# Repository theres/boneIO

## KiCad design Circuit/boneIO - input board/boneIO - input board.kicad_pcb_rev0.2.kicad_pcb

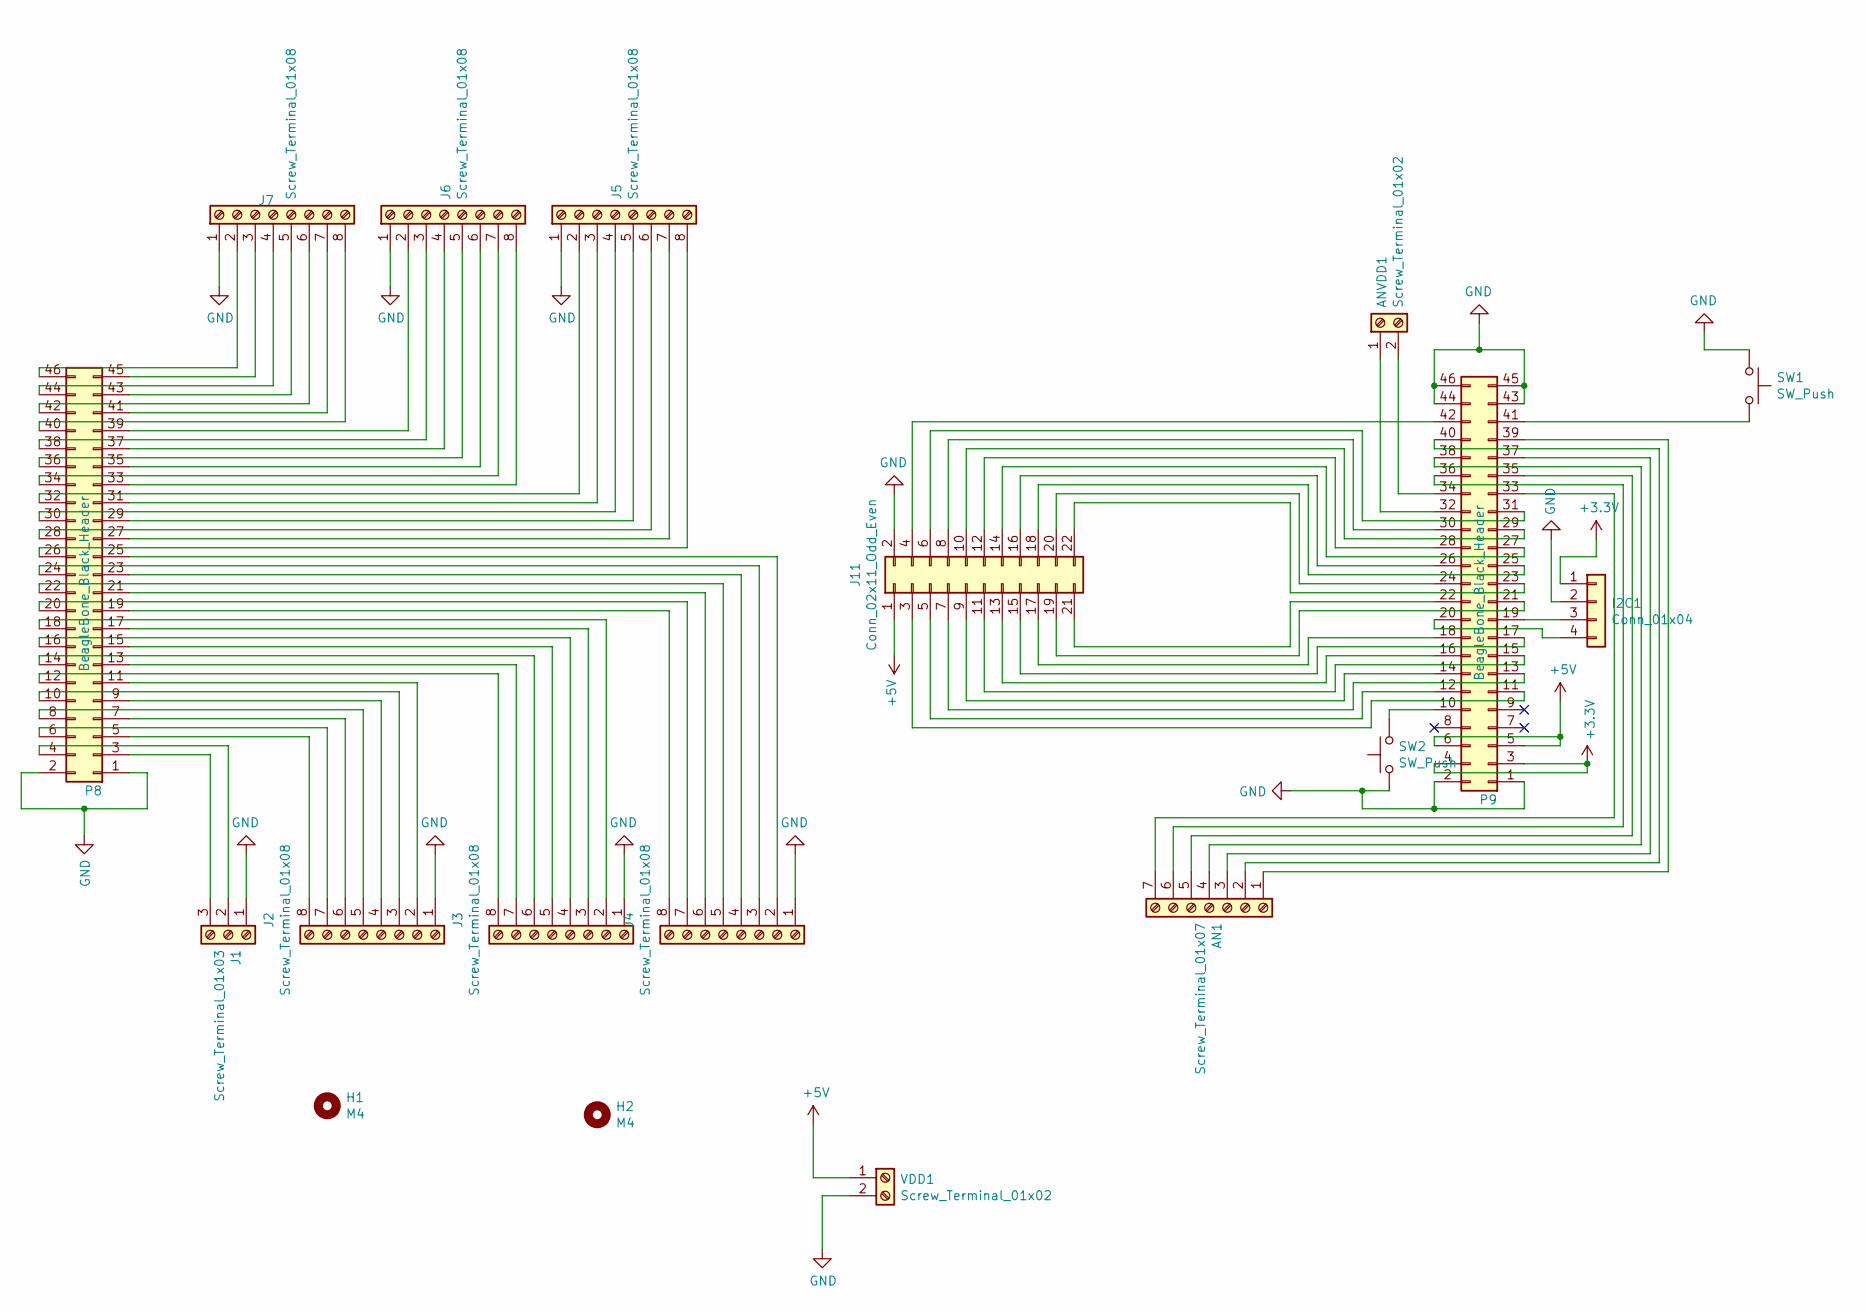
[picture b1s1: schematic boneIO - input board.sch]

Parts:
AN1: Screw_Terminal_01x07; TerminalBlock_RND_205-00017_1x07_P5.00mm_Horizontal
ANVDD1: Screw_Terminal_01x02; TerminalBlock_RND_205-00012_1x02_P5.00mm_Horizontal
H1, H2: M4; MountingHole_4.3mm_M4
I2C1: Conn_01x04; PinHeader_1x04_P2.54mm_Horizontal
J1: Screw_Terminal_01x03; TerminalBlock_RND_205-00013_1x03_P5.00mm_Horizontal
J2, J3, J4, J5, J6, J7: Screw_Terminal_01x08; TerminalBlock_RND_205-00018_1x08_P5.00mm_Horizontal
J11: Conn_02x11_Odd_Even; PinSocket_2x11_P2.54mm_Vertical
P8, P9: BeagleBone_Black_Header; PinHeader_2x23_P2.54mm_Vertical
SW1, SW2: SW_Push; SW_PUSH_6mm_H8mm
VDD1: Screw_Terminal_01x02; TerminalBlock_MetzConnect_Type171_RT13702HBWC_1x02_P7.50mm_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

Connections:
+3V3: I2C1.1, P9.3, P9.4
+5V: J11.1, P9.5, P9.6, VDD1.1
GND: I2C1.2, J1.1, J2.1, J3.1, J4.1, J5.1, J6.1, J7.1, J11.2, P8.1, P8.2, P9.1, P9.2, P9.43, P9.44, P9.45, P9.46, SW1.1, SW2.1, VDD1.2
unnamed: AN1.1, P9.39
unnamed: AN1.2, P9.40
unnamed: AN1.3, P9.37
unnamed: AN1.4, P9.38
unnamed: AN1.5, P9.35
unnamed: AN1.6, P9.36
unnamed: AN1.7, P9.33
unnamed: ANVDD1.1, P9.32
unnamed: ANVDD1.2, P9.34
unnamed: I2C1.3, P9.19
unnamed: I2C1.4, P9.20
unnamed: J1.2, P8.4
unnamed: J1.3, P8.3
unnamed: J2.2, P8.11
unnamed: J2.3, P8.10
unnamed: J2.4, P8.9
unnamed: J2.5, P8.8
unnamed: J2.6, P8.7
unnamed: J2.7, P8.6
unnamed: J2.8, P8.5
unnamed: J3.2, P8.18
unnamed: J3.3, P8.17
unnamed: J3.4, P8.16
unnamed: J3.5, P8.15
unnamed: J3.6, P8.14
unnamed: J3.7, P8.13
unnamed: J3.8, P8.12
unnamed: J4.2, P8.25
unnamed: J4.3, P8.24
unnamed: J4.4, P8.23
unnamed: J4.5, P8.22
unnamed: J4.6, P8.21
unnamed: J4.7, P8.20
unnamed: J4.8, P8.19
unnamed: J5.2, P8.32
unnamed: J5.3, P8.31
unnamed: J5.4, P8.30
unnamed: J5.5, P8.29
unnamed: J5.6, P8.28
unnamed: J5.7, P8.27
unnamed: J5.8, P8.26
unnamed: J6.2, P8.39
unnamed: J6.3, P8.38
unnamed: J6.4, P8.37
unnamed: J6.5, P8.36
unnamed: J6.6, P8.35
unnamed: J6.7, P8.34
unnamed: J6.8, P8.33
unnamed: J7.2, P8.46
unnamed: J7.3, P8.45
unnamed: J7.4, P8.44
unnamed: J7.5, P8.43
unnamed: J7.6, P8.42
unnamed: J7.7, P8.41
unnamed: J7.8, P8.40
unnamed: J11.3, P9.11
unnamed: J11.4, P9.42
unnamed: J11.5, P9.12
unnamed: J11.6, P9.31
unnamed: J11.7, P9.13
unnamed: J11.8, P9.30
unnamed: J11.9, P9.14
unnamed: J11.10, P9.29
unnamed: J11.11, P9.15
unnamed: J11.12, P9.28
unnamed: J11.13, P9.16
unnamed: J11.14, P9.27
unnamed: J11.15, P9.17
unnamed: J11.16, P9.26
unnamed: J11.17, P9.18
unnamed: J11.18, P9.25
unnamed: J11.19, P9.21
unnamed: J11.20, P9.24
unnamed: J11.21, P9.22
unnamed: J11.22, P9.23
unnamed: P9.10, SW2.2
unnamed: P9.41, SW1.2

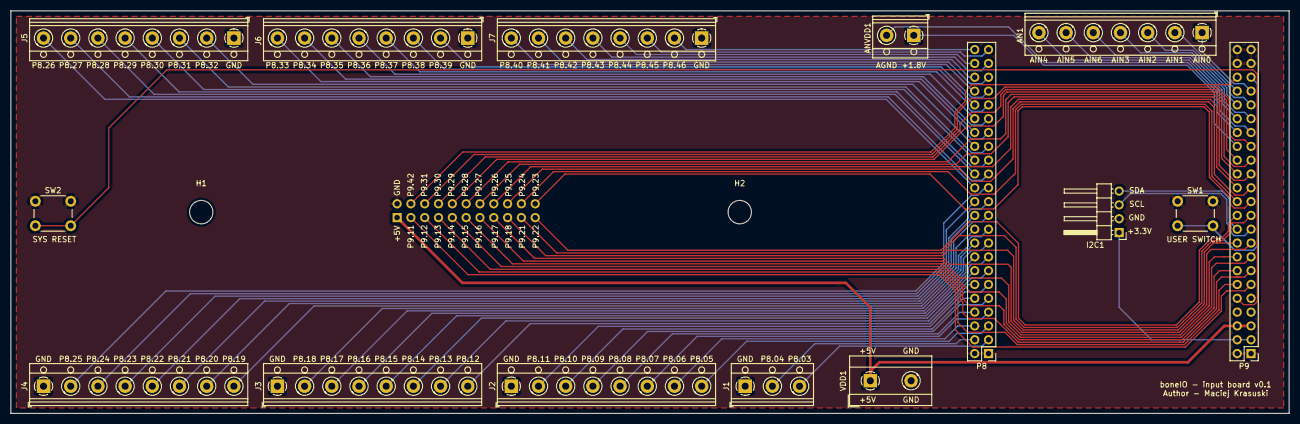
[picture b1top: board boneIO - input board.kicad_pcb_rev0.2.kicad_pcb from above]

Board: 2 copper layers, 235.0 x 74.0 mm, 18 parts (1 on the bottom side), 80 nets.

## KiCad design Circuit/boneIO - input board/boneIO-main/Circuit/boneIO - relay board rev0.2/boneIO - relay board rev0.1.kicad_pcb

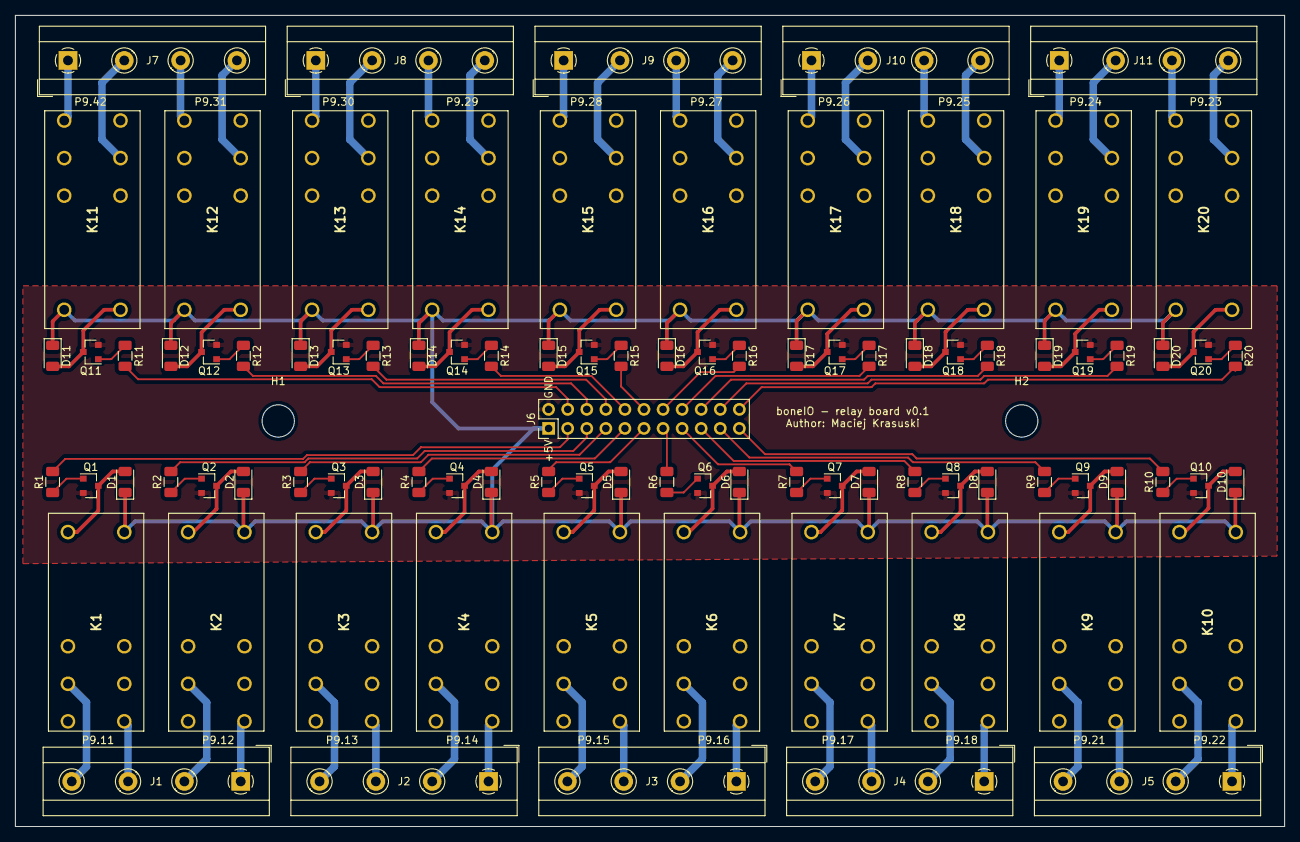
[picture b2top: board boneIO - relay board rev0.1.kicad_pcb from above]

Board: 2 copper layers, 169.0 x 108.0 mm, 93 parts (0 on the bottom side), 102 nets.

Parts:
D1, D2, D3, D4, D5, D6, D7, D8, D9, D10, D11, D12, D13, D14, D15, D16, D17, D18, D19, D20: 1N4148; D_1206_3216Metric
H1, H2: MountingHole; MountingHole_4.3mm_M4
J1, J2, J3, J4, J5, J7, J8, J9, J10, J11: Screw_Terminal_01x04; TerminalBlock_MetzConnect_Type171_RT13704HBWC_1x04_P7.50mm_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
J6: Conn_02x11_Odd_Even; PinHeader_2x11_P2.54mm_Vertical
K1, K2, K3, K4, K5, K6, K7, K8, K9, K10, K11, K12, K13, K14, K15, K16, K17, K18, K19, K20: RM85-2011-35-1005; RM852011351005
Q1, Q2, Q3, Q4, Q5, Q6, Q7, Q8, Q9, Q10, Q11, Q12, Q13, Q14, Q15, Q16, Q17, Q18, Q19, Q20: BC817; SOT-23
R1, R2, R3, R4, R5, R6, R7, R8, R9, R10, R11, R12, R13, R14, R15, R16, R17, R18, R19, R20: 670; R_1206_3216Metric

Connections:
+5V: D1.1, D2.1, D3.1, D4.1, D5.1, D6.1, D7.1, D8.1, D9.1, D10.1, D11.1, D12.1, D13.1, D14.1, D15.1, D16.1, D17.1, D18.1, D19.1, D20.1, J6.1, K1.A2, K2.A2, K3.A2, K4.A2, K5.A2, K6.A2, K7.A2, K8.A2, K9.A2, K10.A2, K11.A2, K12.A2, K13.A2, K14.A2, K15.A2, K16.A2, K17.A2, K18.A2, K19.A2, K20.A2
GND: J6.2, Q1.2, Q2.2, Q3.2, Q4.2, Q5.2, Q6.2, Q7.2, Q8.2, Q9.2, Q10.2, Q11.2, Q12.2, Q13.2, Q14.2, Q15.2, Q16.2, Q17.2, Q18.2, Q19.2, Q20.2
unnamed: D1.2, K1.A1, Q1.3
unnamed: D2.2, K2.A1, Q2.3
unnamed: D3.2, K3.A1, Q3.3
unnamed: D4.2, K4.A1, Q4.3
unnamed: D5.2, K5.A1, Q5.3
unnamed: D6.2, K6.A1, Q6.3
unnamed: D7.2, K7.A1, Q7.3
unnamed: D8.2, K8.A1, Q8.3
unnamed: D9.2, K9.A1, Q9.3
unnamed: D10.2, K10.A1, Q10.3
unnamed: D11.2, K11.A1, Q11.3
unnamed: D12.2, K12.A1, Q12.3
unnamed: D13.2, K13.A1, Q13.3
unnamed: D14.2, K14.A1, Q14.3
unnamed: D15.2, K15.A1, Q15.3
unnamed: D16.2, K16.A1, Q16.3
unnamed: D17.2, K17.A1, Q17.3
unnamed: D18.2, K18.A1, Q18.3
unnamed: D19.2, K19.A1, Q19.3
unnamed: D20.2, K20.A1, Q20.3
unnamed: J1.1, K2.24
unnamed: J1.2, K2.11
unnamed: J1.3, K1.24
unnamed: J1.4, K1.11
unnamed: J2.1, K4.24
unnamed: J2.2, K4.11
unnamed: J2.3, K3.24
unnamed: J2.4, K3.11
unnamed: J3.1, K6.24
unnamed: J3.2, K6.11
unnamed: J3.3, K5.24
unnamed: J3.4, K5.11
unnamed: J4.1, K8.24
unnamed: J4.2, K8.11
unnamed: J4.3, K7.24
unnamed: J4.4, K7.11
unnamed: J5.1, K10.24
unnamed: J5.2, K10.11
unnamed: J5.3, K9.24
unnamed: J5.4, K9.11
unnamed: J6.3, R1.2
unnamed: J6.4, R11.2
unnamed: J6.5, R2.2
unnamed: J6.6, R12.2
unnamed: J6.7, R3.2
unnamed: J6.8, R13.2
unnamed: J6.9, R4.2
unnamed: J6.10, R14.2
unnamed: J6.11, R5.2
unnamed: J6.12, R15.2
unnamed: J6.13, R6.2
unnamed: J6.14, R16.2
unnamed: J6.15, R7.2
unnamed: J6.16, R17.2
unnamed: J6.17, R8.2
unnamed: J6.18, R18.2
unnamed: J6.19, R9.2
unnamed: J6.20, R19.2
unnamed: J6.21, R10.2
unnamed: J6.22, R20.2
unnamed: J7.1, K11.24
unnamed: J7.2, K11.11
unnamed: J7.3, K12.24
unnamed: J7.4, K12.11
unnamed: J8.1, K13.24
unnamed: J8.2, K13.11
unnamed: J8.3, K14.24
unnamed: J8.4, K14.11
unnamed: J9.1, K15.24
unnamed: J9.2, K15.11
unnamed: J9.3, K16.24
unnamed: J9.4, K16.11
unnamed: J10.1, K17.24
unnamed: J10.2, K17.11
unnamed: J10.3, K18.24
unnamed: J10.4, K18.11
unnamed: J11.1, K19.24
unnamed: J11.2, K19.11
unnamed: J11.3, K20.24
unnamed: J11.4, K20.11
unnamed: Q1.1, R1.1
unnamed: Q2.1, R2.1
unnamed: Q3.1, R3.1
unnamed: Q4.1, R4.1
unnamed: Q5.1, R5.1
unnamed: Q6.1, R6.1
unnamed: Q7.1, R7.1
unnamed: Q8.1, R8.1
unnamed: Q9.1, R9.1
unnamed: Q10.1, R10.1
unnamed: Q11.1, R11.1
unnamed: Q12.1, R12.1
unnamed: Q13.1, R13.1
unnamed: Q14.1, R14.1
unnamed: Q15.1, R15.1
unnamed: Q16.1, R16.1
unnamed: Q17.1, R17.1
unnamed: Q18.1, R18.1
unnamed: Q19.1, R19.1
unnamed: Q20.1, R20.1
